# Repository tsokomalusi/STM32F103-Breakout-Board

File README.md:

# STM32F103-Breakout-Board

## Acknowledgements 
The PCB design of this STM32F103 breakout board was inspired by Philip Salmony [Phil's Lab](https://www.youtube.com/watch?v=wLwKgMBWhpY&list=PLXSyc11qLa1b9VA7nw8-DiLRXVhZ2iUN2&index=11).
I reverse-engineered it a bit by adding an SWD connector and ESD protection IC
to  make routing a bit more challenging.

## PCB Layout (2-Layer Design)

## 3D Overview
### Top View

### Bottom View

## JLCPCB Gerber Viewer

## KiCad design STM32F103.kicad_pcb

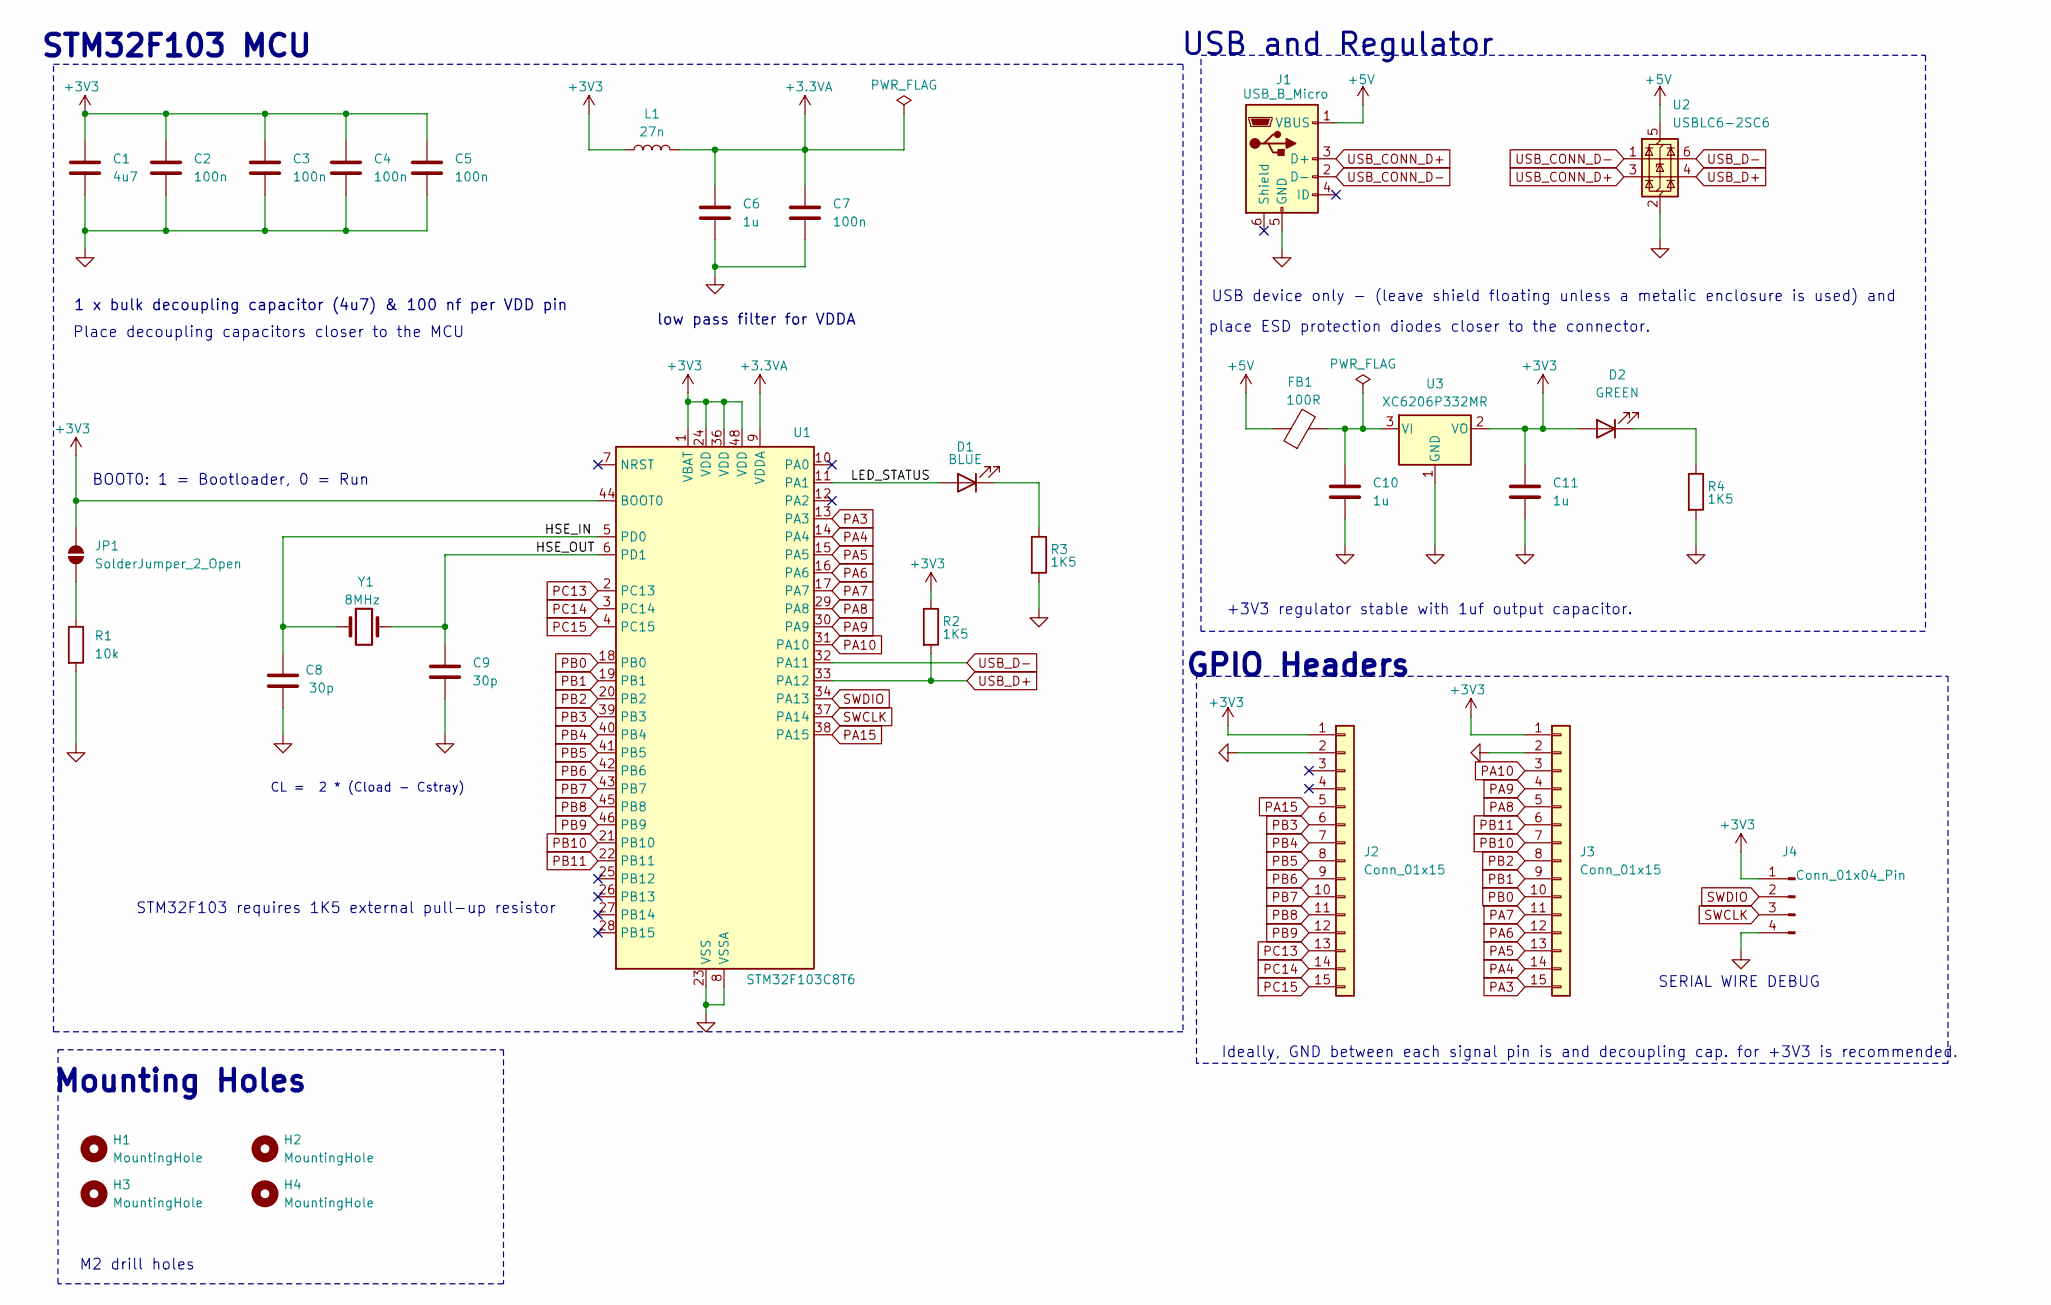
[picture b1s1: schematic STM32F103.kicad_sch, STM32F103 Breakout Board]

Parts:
C1: 4u7; C_0603_1608Metric
C2, C3, C4, C5, C7: 100n; C_0402_1005Metric
C6, C10, C11: 1u; C_0402_1005Metric
C8, C9: 30p; C_0402_1005Metric
D1: BLUE; LED_0603_1608Metric
D2: GREEN; LED_0603_1608Metric
FB1: 100R; L_0805_2012Metric
H1, H2, H3, H4: MountingHole; MountingHole_2.2mm_M2
J1: USB_B_Micro; USB_Micro-B_Wuerth_629105150521
J2, J3: Conn_01x15; PinHeader_1x16_P2.54mm_Vertical
J4: Conn_01x04_Pin; PinHeader_1x04_P2.54mm_Vertical
JP1: SolderJumper_2_Open; SolderJumper-2_P1.3mm_Open_Pad1.0x1.5mm
L1: 27n; L_0402_1005Metric
R1: 10k; R_0402_1005Metric
R2, R3, R4: 1K5; R_0603_1608Metric
U1: STM32F103C8T6; LQFP-48_7x7mm_P0.5mm
U2: USBLC6-2SC6; SOT-23-6
U3: XC6206P332MR; SOT-23-3
Y1: 8MHz; R_0402_1005Metric

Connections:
+3.3VA: C6.1, C7.1, L1.2, U1.9 (VDDA)
+3V3: C1.1, C2.1, C3.1, C4.1, C5.1, C11.1, D2.2 (A), J2.1, J3.1, J4.1, JP1.2 (B), L1.1, R2.1, U1.1 (VBAT), U1.24 (VDD), U1.36 (VDD), U1.44 (BOOT0), U1.48 (VDD), U3.2 (VO)
+5V: FB1.1, J1.1 (VBUS), U2.5 (VBUS)
/HSE_IN: C8.1, U1.5 (PD0), Y1.1
/HSE_OUT: C9.1, U1.6 (PD1), Y1.2
/LED_STATUS: D1.2 (A), U1.11 (PA1)
GND: C1.2, C2.2, C3.2, C4.2, C5.2, C6.2, C7.2, C8.2, C9.2, C10.2, C11.2, J1.5 (GND), J2.2, J3.2, J4.4, R1.2, R3.2, R4.2, U1.8 (VSSA), U1.23 (VSS), U1.35 (VSS), U1.47 (VSS), U2.2 (GND), U3.1 (GND)
unnamed: D1.1 (K), R3.1
unnamed: D2.1 (K), R4.1
unnamed: JP1.1 (A), R1.1
unnamed: C10.1, FB1.2, U3.3 (VI)
PA3: J3.15, U1.13 (PA3)
PA4: J3.14, U1.14 (PA4)
PA5: J3.13, U1.15 (PA5)
PA6: J3.12, U1.16 (PA6)
PA7: J3.11, U1.17 (PA7)
PA8: J3.5, U1.29 (PA8)
PA9: J3.4, U1.30 (PA9)
PA10: J3.3, U1.31 (PA10)
PA15: J2.5, U1.38 (PA15)
PB0: J3.10, U1.18 (PB0)
PB1: J3.9, U1.19 (PB1)
PB2: J3.8, U1.20 (PB2)
PB3: J2.6, U1.39 (PB3)
PB4: J2.7, U1.40 (PB4)
PB5: J2.8, U1.41 (PB5)
PB6: J2.9, U1.42 (PB6)
PB7: J2.10, U1.43 (PB7)
PB8: J2.11, U1.45 (PB8)
PB9: J2.12, U1.46 (PB9)
PB10: J3.7, U1.21 (PB10)
PB11: J3.6, U1.22 (PB11)
PC13: J2.13, U1.2 (PC13)
PC14: J2.14, U1.3 (PC14)
PC15: J2.15, U1.4 (PC15)
SWCLK: J4.3, U1.37 (PA14)
SWDIO: J4.2, U1.34 (PA13)
USB_CONN_D+: J1.3 (D+), U2.3 (I/O2)
USB_CONN_D-: J1.2 (D-), U2.1 (I/O1)
USB_D+: R2.2, U1.33 (PA12), U2.4 (I/O2)
USB_D-: U1.32 (PA11), U2.6 (I/O1)

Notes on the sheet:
M2 drill holes
SERIAL WIRE DEBUG
GPIO Headers
+3V3 regulator stable with 1uf output capacitor.
USB device only - (leave shield floating unless a metalic enclosure is used) and
CL = 2 * (Cload - Cstray)
Place decoupling capacitors closer to the MCU
low pass filter for VDDA
STM32F103 MCU
place ESD protection diodes closer to the connector.
Ideally, GND between each signal pin is and decoupling cap. for +3V3 is recommended.
BOOT0: 1 = Bootloader, 0 = Run
STM32F103 requires 1K5 external pull-up resistor
Mounting Holes
1 x bulk decoupling capacitor (4u7) & 100 nf per VDD pin
USB and Regulator

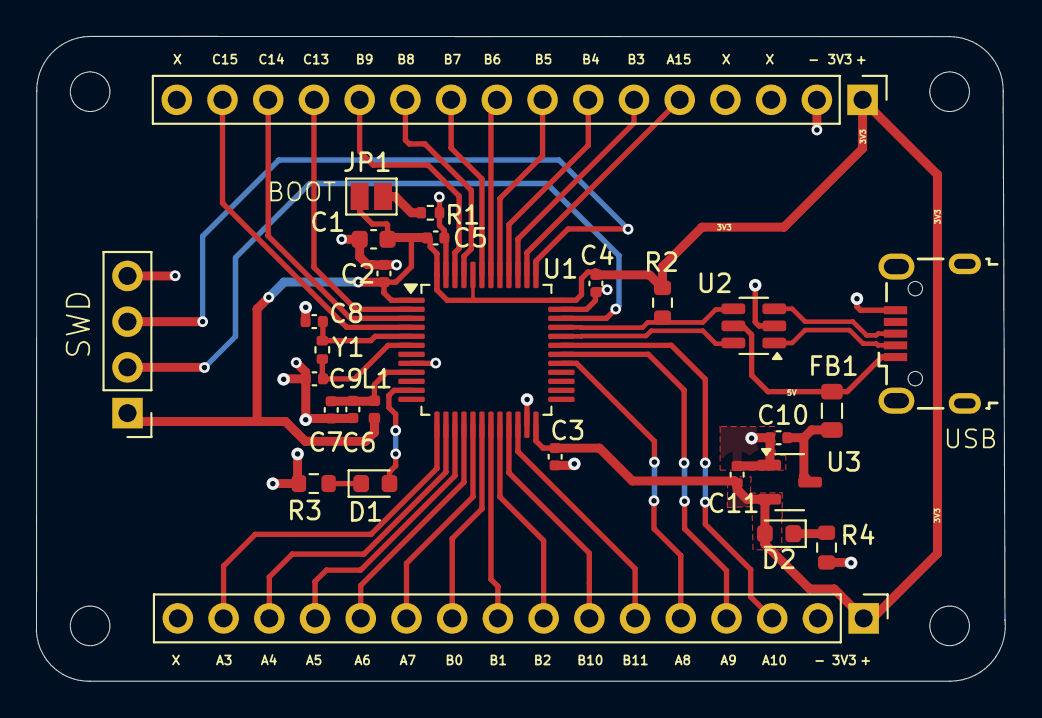
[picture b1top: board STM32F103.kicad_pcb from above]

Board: 2 copper layers, 53.8 x 35.8 mm, 32 parts (0 on the bottom side), 41 nets.
